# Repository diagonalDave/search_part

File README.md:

# Table of Contents

1.  [Search Part](#org4978424)
    1.  [Info](#org4088e50)
    2.  [Installation](#orga82bd6c)
        1.  [Download and setup](#org8908fad)
        2.  [Create the indexes](#orgc109002)
    3.  [Basic Usage](#orge187f09)
    4.  [Search part tools](#orgdddc04e)
    5.  [Examples](#orgfeb9bd0)
        1.  [Refine your regex](#org2f95ea5)

# Search Part

Search part is a proof of concept (POC) part creator for SKIDL. 

Currently the code is good enough for my purposes "Works on my
machine "(TM). But may also be useful for others wishing to use SKIDL more easily.

The main purpose of this POC is to see if it is worthwhile to work it into
SKIDL, provide tests, back port to Python 2 (man get with the times
f-strings are worth it alone) and all the other stuff to make it robust and
reliable on all platforms.

It currently has only been tested on Python 3.8 and pandas 1.15 Windows10
and Python 3.6 and pandas 1.15 on Suse Leap 15.2. Hopefully it will work on
Macs too.

## Info

Creating a part with search part avoids having to know the storage
structure of KiCad parts and footprints.
It is intended to be simple to use:
```
import search_ part as sp
pc = sp.SearchPart()
ldo = pc.create_part(8, "LP2951.*soic", "SOIC") #returns a skidl.Part()
```
To get this simplicity the first part or footprint on the list is
returned, this may not be the part you want or it may blow-up
because no parts were found. This is when you turn to the [1.4](#orgdddc04e)
section below.

The function create\_part is a skidl.Part() wrapper that takes parameters that most designers know:

1.  **pin\_count**
2.  **part\_name**&#x2013;this can be a partial name and is in fact a regex so
    regex symbols can be used. Search\_part provides some tools that
    can help narrow your part search to the correct one. 
    See [Search part tools](#orgdddc04e) section below.
3.  **footprint\_name**, this can be a partial name and is also a 
    regex. See [Search part tools](#orgdddc04e).
4.  **pad\_count**, this by default is set to the pin\_count but sometimes
    these are different.
5.  **\*\*kwargs**, add any key word args you want to pass through to skidl.Part()

## Installation

The installation of search\_part has two parts:

1.  Download and get it setup.
2.  Create the indexes.

### Download and setup

1.  Download or clone the repository onto your system.
2.  pip install pandas 1.15 to the python environment you intend using.
3.  Make sure skidl is installed ;)
4.  Navigate to the search\_part directory. You shoud see:
    -   search\_parts.py
    -   a couple of example files: voltage\_translator\_board\_sp.py and a comparable
        voltage\_translator\_board.py skidl only file.
    -   indexes directory that has two .py files.
    -   pcb\_files directory with some pcb files that use the generated .net files.

### Create the indexes

There are a lot of ways this could be done but using a stone axe
is at least simple if not gratifying.

1.  Navigate to the indexes directory. There are two .py files, if
    the names are confusing stop now this isn't going to work.
2.  Open index\_footprints.py in an editor then head to the bottom
    of the file.
3.  Replace the file path with the one to your kicad **modules**
    directory, some hints are given for common directories in the
    comment.
4.  Save the file open a cmd prompt/terminal then create an index
    with:
    ```
    python index_footprints.py
    ```
This will take 5-10 minutes to run and generate a
skidl\_footprint\_index.csv file.

1.  Repeat steps 2-4 with the index\_parts.py file and your kicad
    **library** directory.

Once this has run for its 5-10 mins it will generate a
skidl\_parts\_index.csv file.

1.  Check the logs to see how it went. Typically all footprint
    files index correctly and there are four part files that wind up in the
    logs. I will look at these when I have a chance.If you need to
    use parts from these files you will have to use skidl.Part() to
    get them on the board.

Test the indexes have been created correctly:

1.  Navigate to the search\_part directory.
2.  Open a python3 terminal then enter:
    ```
    dave@suse-lappy:~/git/python/skidl/search_part> python3 search_part.py
    Create some parts as a test.
    Generate a net list. Check the parts in kicad by importing the search_part.net file.
    
    No errors or warnings found during netlist generation.
    
    Query for all footprints with 5 pads in a dip package.
    Unnamed: 0                                 name  pad_count            location
    8367        8367                     DIP-5-6_W10.16mm          5  Package_DIP.pretty
    8368        8368            DIP-5-6_W10.16mm_LongPads          5  Package_DIP.pretty
    8369        8369                      DIP-5-6_W7.62mm          5  Package_DIP.pretty
    8370        8370             DIP-5-6_W7.62mm_LongPads          5  Package_DIP.pretty
    8371        8371  DIP-5-6_W7.62mm_SMDSocket_SmallPads          5  Package_DIP.pretty
    8372        8372               DIP-5-6_W7.62mm_Socket          5  Package_DIP.pretty
    8373        8373      DIP-5-6_W7.62mm_Socket_LongPads          5  Package_DIP.pretty
    8374        8374   DIP-5-6_W8.89mm_SMDSocket_LongPads          5  Package_DIP.pretty
    >>>
    ```
If you see the above then you are ready to go. 
If not:

1.  Check the index logs and the index.csv files (they should both be around 1MB in size).

## Basic Usage

1.  Create a python file in the search\_part directory.
2.  Import skidl and search\_part then start building your skidl
    circuit. 
    ```
    import skidl
    import search_part as sp
    part_creator = sp.SearchPart()
    r5v = part_creator.create_part(2, "R", "R_1206", ref="R5V", value="10k")
    &#x2026;
    use the part
    &#x2026;
    r5v[1] += V5
    r5v[2] += input_net
    ```

The voltage\_translator\_sp.py file provides example usage.

## Search part tools

Two further functions are provided with search\_part that allow you
to interogate the indexes: query\_part\_return\_all(pin\_count,
part\_name) and query\_footprint\_return\_all(pad\_count,
footprint\_name)

Search\_part uses case insensitive regexes to filter the dataset it then
uses the first record to create the part. This is simple but can cause an
exception if nothing is returned or you get the wrong part or footprint
sent to the board file.  The process to refine a regex described below
takes about 30 seconds at the interpreter. The regexes are simple and only
use a few operators to reduce the filtered dataset to what you want.

1.  Open a python interpreter in the search\_part directory.
```
>>> import search_part as sp
>>> pp = sp.SearchPart()
>>> pp.query_part_return_all(4, "conn")
   Unnamed: 0                     part_name  &#x2026;                                           location                         alias
   2459          11                    CONN_01X04  &#x2026;         D:\APPS\KiCad\share\kicad\library\conn.lib                    CONN_01X04
   2497          49                    CONN_02X02  &#x2026;         D:\APPS\KiCad\share\kicad\library\conn.lib
   ...
   3463           2           Conn_01x03_Shielded  &#x2026;  D:\APPS\KiCad\share\kicad\library\Connector_Ge&#x2026;           Conn_01x03_Shielded

[13 rows x 5 columns]
>>> pp.query_footprint_return_all(4, "pinHeader.*vertical")
   Unnamed: 0                                           name  pad_count                           location
   918          918             FanPinHeader_1x04_P2.54mm_Vertical          4                   Connector.pretty
   ...
   4946        4946                PinHeader_2x02_P2.54mm_Vertical          4  Connector_PinHeader_2.54mm.pretty
   4947        4947            PinHeader_2x02_P2.54mm_Vertical_SMD          4  Connector_PinHeader_2.54mm.pretty
   >>>
```
From these results you can see that refining the footprint name
will be needed to get the right spacing and orientation, see
[1.5.1](#org2f95ea5) for an example of refining the footprint name.

## Examples

Some example files have been provided in the search\_part directory
to illustrate skidl and search\_part usage. There is nothing high
falutin' about the examples and I expect it will change as I become
more familiar with skidl for pcbs. 
voltage\_translator\_board\_sp.py is the search\_part/skidl version
voltage\_translator\_board.py is the skidl only version this board was
layed out and sent for fabrication.

### Refine your regex

To be blunt regexes can be painful, hopefully this section will
allow you to easily get the part or footprint to the top of the
filtered list.
Let's start with a standard 4 pin header used on just about any
prototyping board. 

1.  Try something simple:
```
>>> pp.query_footprint_return_all(4, "pinHeader")
```
Returns a shipload of results starting with 'FanPinHeader' &#x2026;

There are two possibilities here:

-   search the list manually, find your part and  copy and paste the full text into

create\_part. You are now done. Or;

-   refine the regex.

The following describes how to refine the regex.

Looking at these results you realise that specifying the pin
spacing is important, they make more than one kind!

 Try again
```
>>> pp.query_footprint_return_all(4, "pinHeader.*2.54")
```
Adding a '\.*' means anything can be between 'pinHeader' and '2.54'
This reduces the list to:
```
>>> pp.query_footprint_return_all(4, "pinHeader.*2.54")
  Unnamed: 0                                           name  pad_count                           location
  918          918             FanPinHeader_1x04_P2.54mm_Vertical          4                   Connector.pretty
  4794        4794              PinHeader_1x04_P2.54mm_Horizontal          4  Connector_PinHeader_2.54mm.pretty
  4795        4795                PinHeader_1x04_P2.54mm_Vertical          4  Connector_PinHeader_2.54mm.pretty
  ...
  4946        4946                PinHeader_2x02_P2.54mm_Vertical          4  Connector_PinHeader_2.54mm.pretty
  4947        4947            PinHeader_2x02_P2.54mm_Vertical_SMD          4  Connector_PinHeader_2.54mm.pretty
  >>>
```
Looking through the list again you realise orientation needs
to be specified.

Try again
```   
    >>> pp.query_footprint_return_all(4, "pinHeader.*2.54.*vertical")
     Unnamed: 0                                           name  pad_count                           location
     
     918          918             FanPinHeader_1x04_P2.54mm_Vertical          4                   Connector.pretty
     4795        4795                PinHeader_1x04_P2.54mm_Vertical          4  Connector_PinHeader_2.54mm.pretty
     4796        4796   PinHeader_1x04_P2.54mm_Vertical_SMD_Pin1Left          4  Connector_PinHeader_2.54mm.pretty
     4797        4797  PinHeader_1x04_P2.54mm_Vertical_SMD_Pin1Right          4  Connector_PinHeader_2.54mm.pretty
     4946        4946                PinHeader_2x02_P2.54mm_Vertical          4  Connector_PinHeader_2.54mm.pretty
     4947        4947            PinHeader_2x02_P2.54mm_Vertical_SMD          4  Connector_PinHeader_2.54mm.pretty
     >>>
```
OK getting closer I don't want no smd pin header. A bit of
contemplation give you the realisation that the bits you want end
with 'Vertical'.

Try again
```    
    >>> pp.query_footprint_return_all(4, "pinHeader.*2.54.*vertical$")
    Unnamed: 0                                name  pad_count                           location

    918          918  FanPinHeader_1x04_P2.54mm_Vertical          4                   Connector.pretty
    4795        4795     PinHeader_1x04_P2.54mm_Vertical          4  Connector_PinHeader_2.54mm.pretty
    4946        4946     PinHeader_2x02_P2.54mm_Vertical          4  Connector_PinHeader_2.54mm.pretty
    >>>
```
The $ sign at the end means that 'vertical' has to be at the end
of the line.

Now ffs what is with the 'FanPinHeader'? It has resolutely stayed
at the top of the list. Its got to go.
```
  >>> pp.query_footprint_return_all(4, "^pinHeader.*2.54.*vertical$")
  Unnamed: 0                             name  pad_count                           location
  4795        4795  PinHeader_1x04_P2.54mm_Vertical          4  Connector_PinHeader_2.54mm.pretty
  4946        4946  PinHeader_2x02_P2.54mm_Vertical          4  Connector_PinHeader_2.54mm.pretty
  >>>
```
The '^' sign at the beginning means 'pinHeader' is the first thing
on the line.
You could leave it here and search\_part will use the first
footprint, but for completeness we will get rid of the remaining
option by adding "\_1" to 'pinHeader'
```
>>> pp.query_footprint_return_all(4, "^pinHeader_1.*2.54.*vertical$")
Unnamed: 0                             name  pad_count                           location
4795        4795  PinHeader_1x04_P2.54mm_Vertical          4  Connector_PinHeader_2.54mm.pretty
>>>
```
While it takes a chunk of time to read and write this process it happens quickly
with the interpreter so the above could occur in less than 30 seconds with a
little experience.

Once you have the correct regex copy and paste into your
create\_part field to get it every time.

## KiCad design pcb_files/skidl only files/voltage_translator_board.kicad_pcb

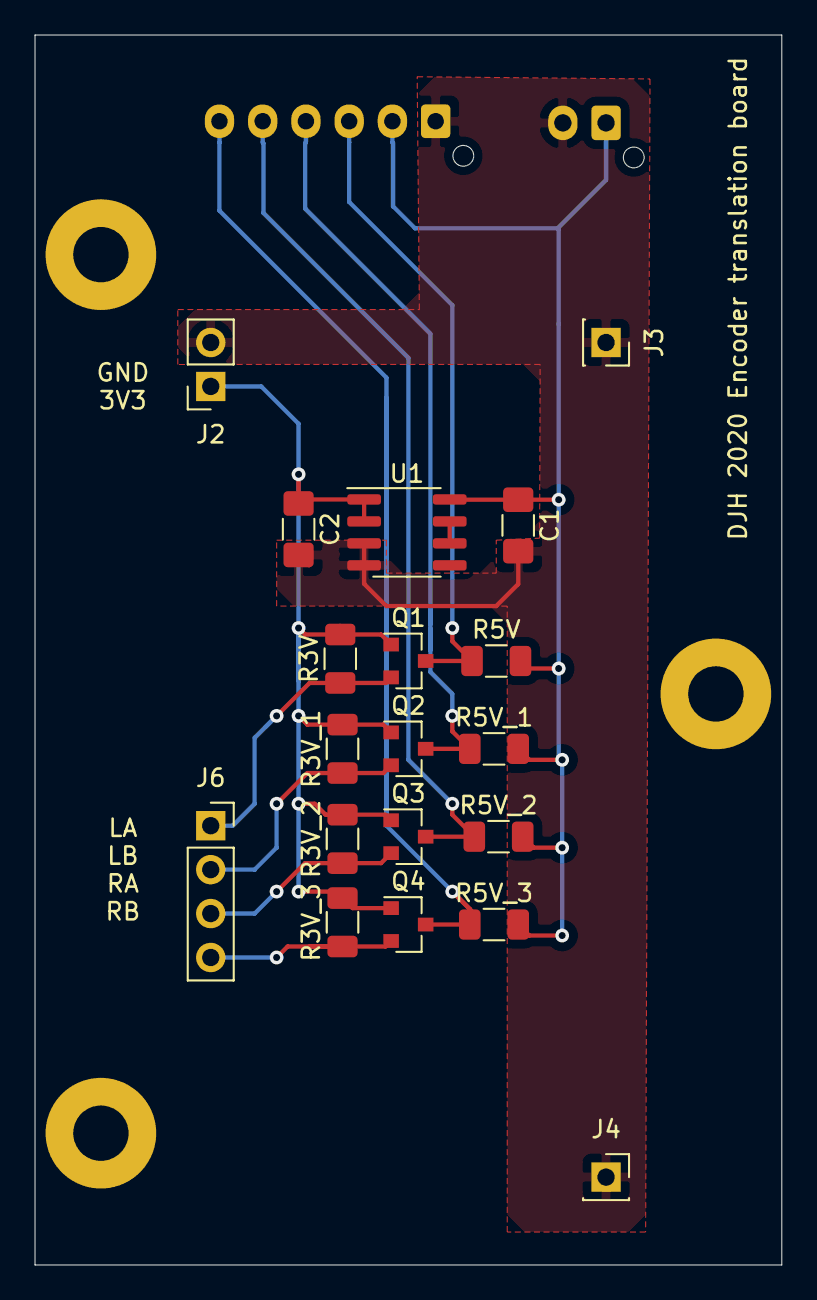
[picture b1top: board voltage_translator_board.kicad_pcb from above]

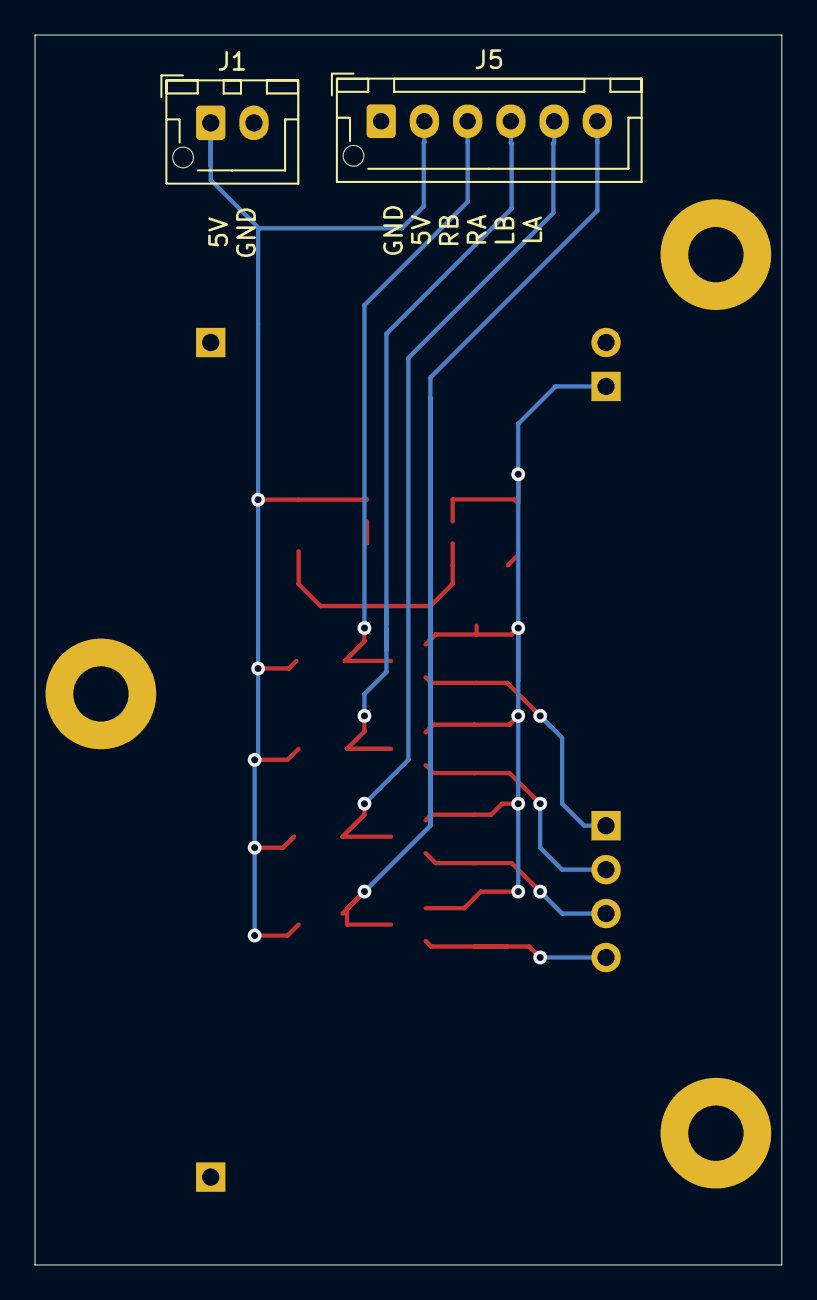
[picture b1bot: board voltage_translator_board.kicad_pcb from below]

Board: 2 copper layers, 43.2 x 71.1 mm, 24 parts (2 on the bottom side), 12 nets.

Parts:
 : Mount; MountingHole_3.2mm_M3_Pad
 #2,  #3: Mount; MountingHole_3.2mm_M3_Pad
C1, C2: 10uF; C_1206_3216Metric_Pad1.42x1.75mm_HandSolder
J1: Conn_01x02_Male; JST_XH_B2B-XH-AM_1x02_P2.50mm_Vertical
J2: PSOC_Power; PinSocket_1x02_P2.54mm_Vertical
J3, J4: Support; PinSocket_1x01_P2.54mm_Vertical
J5: Conn_01x06_Male; JST_XH_B6B-XH-AM_1x06_P2.50mm_Vertical
J6: PSOC_enc; PinSocket_1x04_P2.54mm_Vertical
Q1, Q2, Q3, Q4: BSS138; SOT-23
R3V, R3V_1, R3V_2, R3V_3, R5V, R5V_1, R5V_2, R5V_3: 10k; R_1206_3216Metric
U1: LP2951-3.0_SOIC; SOIC-8_3.9x4.9mm_P1.27mm

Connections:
3V3: C2.1, J2.1, Q1.1, Q2.1, Q3.1, Q4.1, R3V.2, R3V_1.2, R3V_2.2, R3V_3.2, U1.1, U1.2
5V: C1.1, J1.1, J5.2, R5V.2, R5V_1.2, R5V_2.2, R5V_3.2, U1.8
GND: C1.2, C2.2, J1.2, J2.2, J3.1, J4.1, J5.1, U1.3, U1.4
unnamed: U1.6, U1.7
high_in0: J5.3, Q1.3, R5V.1
high_in1: J5.4, Q2.3, R5V_1.1
high_in2: J5.5, Q3.3, R5V_2.1
high_in3: J5.6, Q4.3, R5V_3.1
low_out0: J6.1, Q1.2, R3V.1
low_out1: J6.2, Q2.2, R3V_1.1
low_out2: J6.3, Q3.2, R3V_2.1
low_out3: J6.4, Q4.2, R3V_3.1

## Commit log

2020-12-07 Fixed some formatting issues.
2020-12-07 Further formatting changes.
2020-12-07 Guess and check md format
2020-12-15 Removed unwanted backslash
